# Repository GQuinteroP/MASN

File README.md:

# MASN: Mobile Acoustic Sensor Node

The **MASN** is an advanced, low-power sensor node designed for high-fidelity acoustic monitoring and long-range data transmission via NB-IoT. This repository contains the complete hardware design files, firmware, and configuration tools.

## Project Status: Minimal Working Version (MWV)
**Note:** The current firmware implementation is a **minimal working version**. While the hardware is fully featured, the firmware does not yet implement all architectural capabilities described in the documentation. Users are encouraged to consult the **Roadmap** below for contribution opportunities.

## Hardware Overview

The hardware architecture is optimized for power efficiency and modular operation, featuring a specialized dual-voltage design.

### Technical Specifications
* **Microcontroller:** STM32L452RET6P (Ultra-low-power ARM Cortex-M4).
* **Acoustic Sensing:** SPH0645LM4H MEMS microphone.
* **Positioning:** MAX-M10S-00B GNSS module.
* **Connectivity:** SIMCOM SIM7022 NB-IoT module.
* **Storage:** M95P32-IXMNT/E ultra-low-power EEPROM (32 Mbit).
* **Interface:** USB-C for parameter configuration, calibration, and data recovery.

### Architecture and PCB Design
The MASN is implemented on a double-sided printed circuit board (PCB). The architecture utilizes two isolated voltage domains:
1.  **1.8 V Domain (Front Face):** Powers the MCU, GNSS, microphone, and EEPROM.
2.  **2.1 V Domain (Back Face):** Powers the NB-IoT communication components.

---

## Firmware & Software

### Firmware Description (Current Implementation)
The firmware is built on **FreeRTOS**, following the architecture proposed in Quintero-Perez et al. (2026). It enables concurrent execution of four primary tasks:
* **Sampling:** Continuous audio acquisition using DMA and I2S protocol at $F_s = 32$ kHz.
* **Signal Processing:** Basic computation of $L_{Aeq}$ and OTOB indices ($L_{eq, f_c}$).
* **Georeferencing (GNSS):** Interfacing with the MAX-M10S module to retrieve latitude, longitude, satellite count (Sat#), and fix quality (Q). This metadata is integrated into the acoustic data blocks.
* **Transmission:** Support for network attachment and data delivery via **CoAP protocol** over NB-IoT.

### Configuration GUI
A Python-based GUI facilitates node management via USB-C:
* **Location:** `/Software/CONFIG_GUI`
* **Features:** Time synchronization, module management (GNSS/NB-IoT), and sensor calibration.

---

## Roadmap & Known Issues

### To-Do (Pending Features)
- [ ] **125 ms Sampling:** Implement granular chunking for high-resolution analysis.
- [ ] **IMEI Management:** Read IMEI once and store in non-volatile memory to reduce startup overhead.
- [ ] **Auto-Time Sync:** Automatic RTC configuration based on GNSS NMEA sentences.
- [ ] **EEPROM Integration:** Full implementation of data caching during network outages.

### Known Bugs & Technical Debt
- **Prescaler Drift:** Issues observed with prescaler stability over very long-term operation.
- **Communication Inefficiency:** Optimization required for both NB-IoT module and USB-C serial communication stacks.
- **Interrupt Overhead:** High processing load within `HAL_UART_RxCpltCallback`; logic needs to be migrated to task-level processing.

---

## Citation

If you use this hardware or software in your research, please cite the following paper:

> Quintero, G., Balastegui, A., & Romeu, J. (2026). **Autonomous mobile low-cost sensor node for high-resolution noise sampling in urban environments**. *Measurement*. (Accepted, pending publication).

---

## Licensing

### Hardware
Licensed under **CERN Open Hardware Licence Version 2 - Strongly Reciprocal (CERN-OHL-S)**.
* Full text: `docs/CERN-OHL-S.txt`

### Firmware & Software
Licensed under **GNU General Public License v3.0 (GPL-3.0)**.
* Full text: `docs/GNU GPL v3.txt`

---

## Repository Structure
* `/PCB`: Schematics, PCB design files, and BOM.
* `/Firmware`: Source code and build files for STM32.
* `/Software/CONFIG_GUI`: Python source code and UI files.
* `/docs`: Technical documentation, implementation images, and license files.

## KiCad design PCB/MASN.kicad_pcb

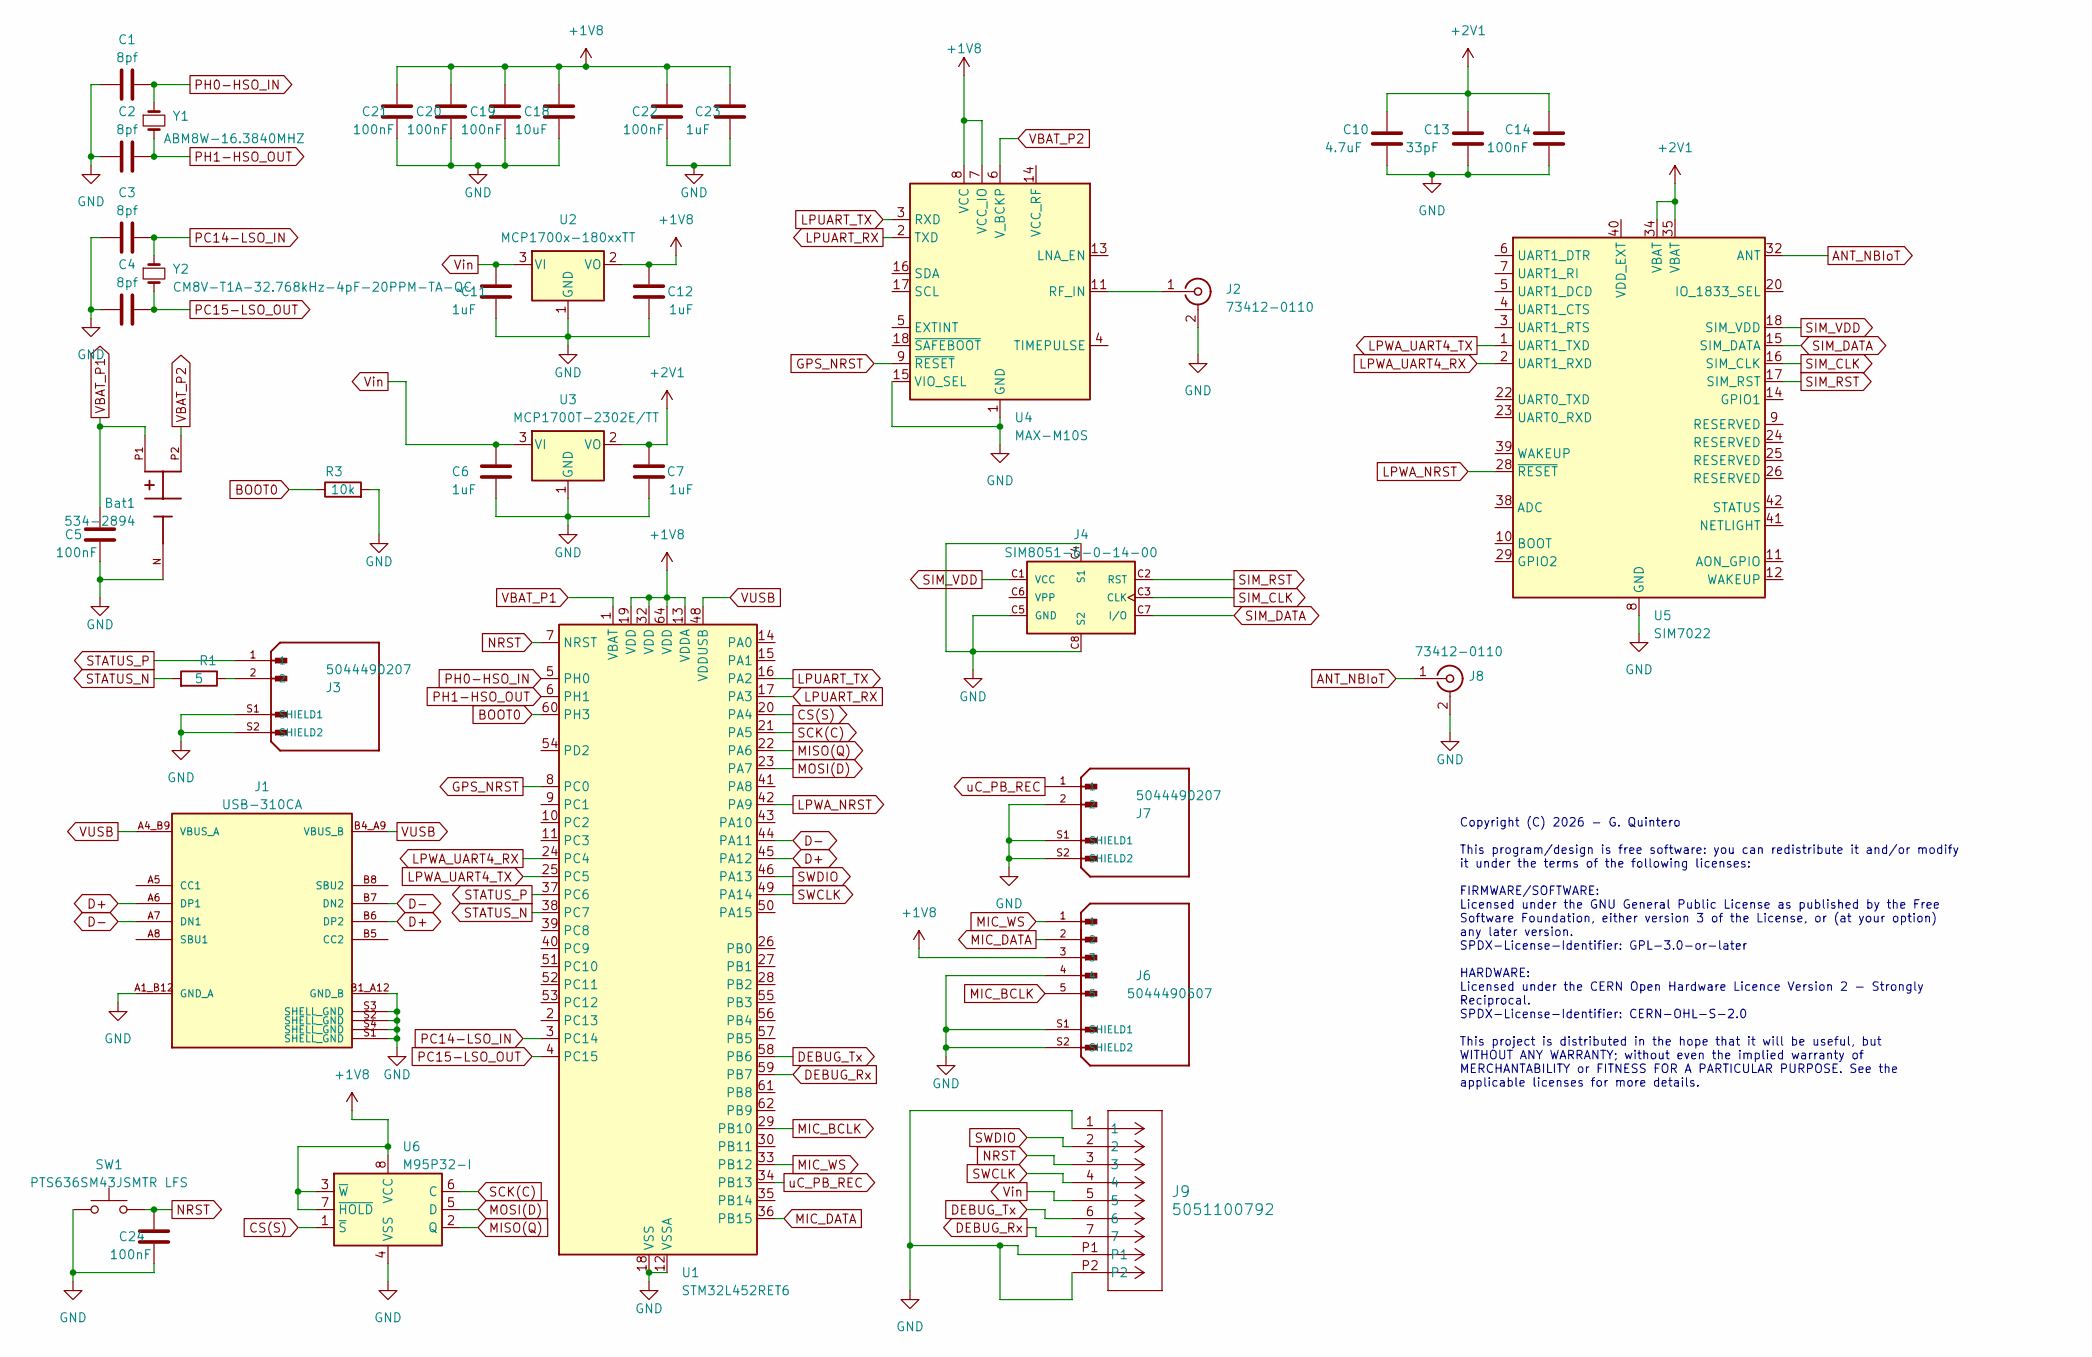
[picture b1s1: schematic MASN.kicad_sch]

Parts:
Bat1: 534-2894; BAT_2894; PARTREV B
C1, C2, C3, C4: 8pf; C_0603_1608Metric_Pad1.08x0.95mm_HandSolder
C5, C14, C19, C20, C21, C22, C24: 100nF; C_0603_1608Metric_Pad1.08x0.95mm_HandSolder
C6, C7, C11, C12, C23: 1uF; C_0603_1608Metric_Pad1.08x0.95mm_HandSolder
C10: 4.7uF; C_0603_1608Metric_Pad1.08x0.95mm_HandSolder
C13: 33pF; C_0603_1608Metric_Pad1.08x0.95mm_HandSolder
C18: 10uF; C_0603_1608Metric_Pad1.08x0.95mm_HandSolder
J1: USB-310CA; USB-C-SMD_20P-P0.50-L6.5-W11.2; PARTREV A
J2, J8: 73412-0110; U.FL_Molex_MCRF_73412-0110_Vertical
J3, J7: 5044490207; MOLEX_5044490207; PARTREV A
J4: SIM8051-6-0-14-00; GCT_SIM8051-6-0-14-00-X-REVD
J6: 5044490507; MOLEX_5044490507; PARTREV A
J9: 5051100792; CON_5051100792_MOL
R1: 5; R_0603_1608Metric_Pad0.98x0.95mm_HandSolder
R3: 10k; R_0603_1608Metric_Pad0.98x0.95mm_HandSolder
SW1: PTS636SM43JSMTR LFS; SW_SPST_CK_RS282G05A3
U1: STM32L452RET6; LQFP-64_10x10mm_P0.5mm
U2: MCP1700x-180xxTT; SOT-23
U3: MCP1700T-2302E/TT; SOT-23
U4: MAX-M10S; ublox_MAX
U5: SIM7022; SIMCom_SIM800C
U6: M95P32-I; SOIC-8_3.9x4.9mm_P1.27mm
Y1: ABM8W-16.3840MHZ; Crystal_SMD_Abracon_ABM8G-4Pin_Custom
Y2: CM8V-T1A-32.768kHz-4pF-20PPM-TA-QC; Crystal_SMD_MicroCrystal_CC8V-T1A-2Pin_2.0x1.2mm_HandSolder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

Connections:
+1V8: C12.2, C18.2, C19.2, C20.2, C21.2, C22.2, C23.2, J6.3, U1.13 (VDDA), U1.19 (VDD), U1.32 (VDD), U1.64 (VDD), U2.2 (VO), U4.7 (VCC_IO), U4.8 (VCC), U6.3 (~W), U6.7 (~HOLD), U6.8 (VCC)
+2V1: C7.2, C10.2, C13.2, C14.2, U3.2 (VO), U5.34 (VBAT), U5.35 (VBAT)
ANT_NBIoT: J8.1 (In), U5.32 (ANT)
BOOT0: R3.1, U1.60 (PH3)
CS(S): U1.20 (PA4), U6.1 (~S)
D+: J1.A6 (DP1), J1.B6 (DP2), U1.45 (PA12)
D-: J1.A7 (DN1), J1.B7 (DN2), U1.44 (PA11)
DEBUG_Rx: J9.7, U1.59 (PB7)
DEBUG_Tx: J9.6, U1.58 (PB6)
GND: Bat1.N, C1.2, C2.1, C3.2, C4.1, C5.1, C6.1, C7.1, C10.1, C11.1, C12.1, C13.1, C14.1, C18.1, C19.1, C20.1, C21.1, C22.1, C23.1, C24.1, J1.A1_B12 (GND_A), J1.B1_A12 (GND_B), J1.S1 (SHELL_GND), J1.S2 (SHELL_GND), J1.S3 (SHELL_GND), J1.S4 (SHELL_GND), J2.2 (Ext), J3.S1 (SHIELD1), J3.S2 (SHIELD2), J4.C4 (S1), J4.C5 (GND), J4.C8 (S2), J6.4, J6.S1 (SHIELD1), J6.S2 (SHIELD2), J7.2, J7.S1 (SHIELD1), J7.S2 (SHIELD2), J8.2 (Ext), J9.1, J9.P1, J9.P2, R3.2, SW1.1, U1.12 (VSSA), U1.18 (VSS), U1.31 (VSS), U1.47 (VSS), U1.63 (VSS), U2.1 (GND), U3.1 (GND), U4.1 (GND), U4.10 (GND), U4.12 (GND), U4.15 (VIO_SEL), U5.8 (GND), U5.13 (GND), U5.19 (GND), U5.21 (GND), U5.27 (GND), U5.30 (GND), U5.31 (GND), U5.33 (GND), U5.36 (GND), U5.37 (GND), U6.4 (VSS)
GPS_NRST: U1.8 (PC0), U4.9 (~RESET)
LPUART_RX: U1.17 (PA3), U4.2 (TXD)
LPUART_TX: U1.16 (PA2), U4.3 (RXD)
LPWA_NRST: U1.42 (PA9), U5.28 (~RESET)
LPWA_UART4_RX: U1.24 (PC4), U5.2 (UART1_RXD)
LPWA_UART4_TX: U1.25 (PC5), U5.1 (UART1_TXD)
MIC_BCLK: J6.5, U1.29 (PB10)
MIC_DATA: J6.2, U1.36 (PB15)
MIC_WS: J6.1, U1.33 (PB12)
MISO(Q): U1.22 (PA6), U6.2 (Q)
MOSI(D): U1.23 (PA7), U6.5 (D)
NRST: C24.2, J9.3, SW1.2, U1.7 (NRST)
unnamed: J2.1 (In), U4.11 (RF_IN)
unnamed: J3.2, R1.1
PC14-LSO_IN: C3.1, U1.3 (PC14), Y2.1
PC15-LSO_OUT: C4.2, U1.4 (PC15), Y2.2
PH0-HSO_IN: C1.1, U1.5 (PH0), Y1.1
PH1-HSO_OUT: C2.2, U1.6 (PH1), Y1.3
SCK(C): U1.21 (PA5), U6.6 (C)
SIM_CLK: J4.C3 (CLK), U5.16 (SIM_CLK)
SIM_DATA: J4.C7 (I/O), U5.15 (SIM_DATA)
SIM_RST: J4.C2 (RST), U5.17 (SIM_RST)
SIM_VDD: J4.C1 (VCC), U5.18 (SIM_VDD)
STATUS_N: R1.2, U1.38 (PC7)
STATUS_P: J3.1, U1.37 (PC6)
SWCLK: J9.4, U1.49 (PA14)
SWDIO: J9.2, U1.46 (PA13)
VBAT_P1: Bat1.P1, C5.2, U1.1 (VBAT)
VBAT_P2: Bat1.P2, U4.6 (V_BCKP)
VUSB: J1.A4_B9 (VBUS_A), J1.B4_A9 (VBUS_B), U1.48 (VDDUSB)
Vin: C6.2, C11.2, J9.5, U2.3 (VI), U3.3 (VI)
uC_PB_REC: J7.1, U1.34 (PB13)

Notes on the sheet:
Copyright (C) 2026 - G. Quintero This program/design is free software: you can redistribute it and/or modify it under the terms of the following licenses: FIRMWARE/SOFTWARE: Licensed under the GNU General Public License as published by the Free Software Foundation, either version 3 of the License, 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

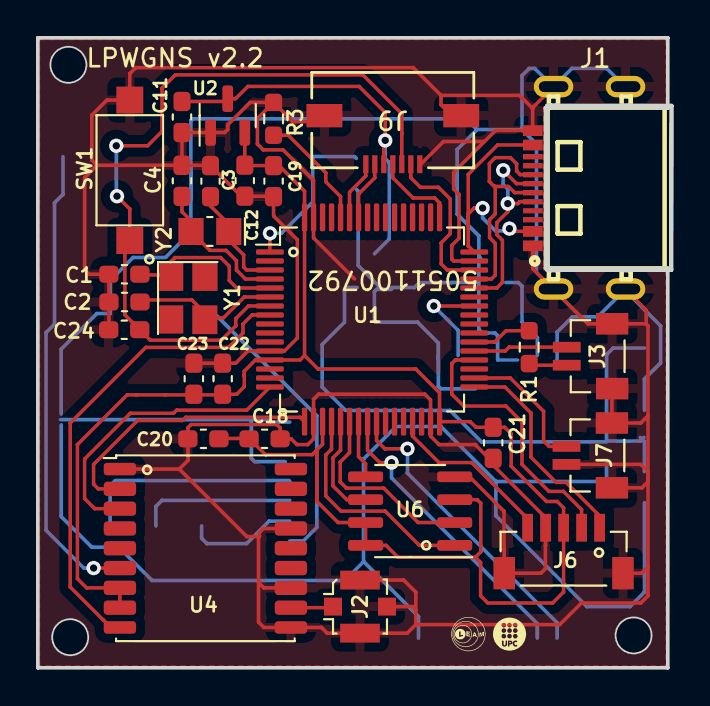
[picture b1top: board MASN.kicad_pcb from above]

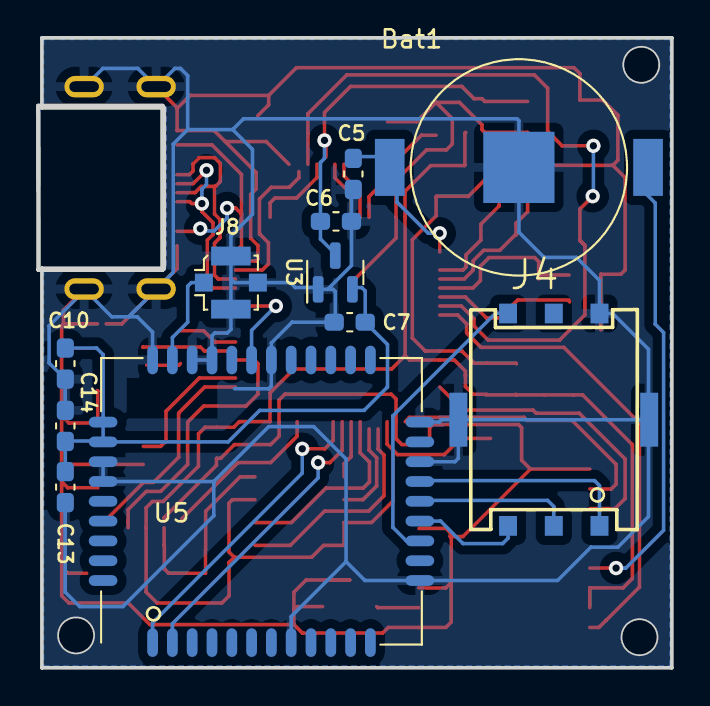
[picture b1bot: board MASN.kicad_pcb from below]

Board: 2 copper layers, 35.2 x 34.9 mm, 39 parts (11 on the bottom side), 42 nets.

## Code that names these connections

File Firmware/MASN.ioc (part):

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Mcu.Name=STM32L452R(C-E)Tx
Mcu.Package=LQFP64
Mcu.UserName=STM32L452RETx
PA11.Mode=Device
PA11.Signal=USB_DM
PA12.Mode=Device
PA12.Signal=USB_DP
PA13\ (JTMS/SWDIO).GPIOParameters=GPIO_Label
PA13\ (JTMS/SWDIO).GPIO_Label=TMS
PA13\ (JTMS/SWDIO).Mode=Serial_Wire
PA13\ (JTMS/SWDIO).Signal=SYS_JTMS-SWDIO
PA14\ (JTCK/SWCLK).GPIOParameters=GPIO_Label
PA14\ (JTCK/SWCLK).GPIO_Label=TCK
PA14\ (JTCK/SWCLK).Mode=Serial_Wire
PA14\ (JTCK/SWCLK).Signal=SYS_JTCK-SWCLK
PA2.GPIOParameters=GPIO_Label
PA2.GPIO_Label=LPUART_GPS_Tx
PA2.Mode=Asynchronous
PA2.Signal=LPUART1_TX
PA3.GPIOParameters=GPIO_PuPd,GPIO_Label
PA3.GPIO_Label=LPUART_GPS_Rx
PA3.GPIO_PuPd=GPIO_PULLUP
PA3.Mode=Asynchronous
PA3.Signal=LPUART1_RX
PA4.GPIOParameters=GPIO_Speed,PinState,GPIO_Label
PA4.GPIO_Label=SPI1_CS
PA4.GPIO_Speed=GPIO_SPEED_FREQ_VERY_HIGH
PA4.PinState=GPIO_PIN_RESET
PA4.Signal=GPIO_Output
PA5.GPIOParameters=GPIO_PuPd
PA5.GPIO_PuPd=GPIO_NOPULL
PA5.Mode=Full_Duplex_Master
PA5.Signal=SPI1_SCK
PA6.GPIOParameters=GPIO_PuPd
PA6.GPIO_PuPd=GPIO_NOPULL
PA6.Mode=Full_Duplex_Master
PA6.Signal=SPI1_MISO
PA7.GPIOParameters=GPIO_PuPd
PA7.GPIO_PuPd=GPIO_NOPULL
PA7.Mode=Full_Duplex_Master
PA7.Signal=SPI1_MOSI
PA9.GPIOParameters=GPIO_Speed,PinState,GPIO_PuPd,GPIO_Label
PA9.GPIO_Label=LPWA_NRST
PA9.GPIO_PuPd=GPIO_PULLUP
PA9.GPIO_Speed=GPIO_SPEED_FREQ_HIGH
PA9.PinState=GPIO_PIN_RESET
PA9.Signal=GPIO_Output
PB10.Mode=SAI_A_Master
PB10.Signal=SAI1_SCK_A
PB12.Mode=SAI_A_Master
PB12.Signal=SAI1_FS_A
PB13.GPIOParameters=GPIO_PuPd,GPIO_Label,GPIO_ModeDefaultEXTI
PB13.GPIO_Label=PB_REC
PB13.GPIO_ModeDefaultEXTI=GPIO_MODE_IT_FALLING
PB13.GPIO_PuPd=GPIO_PULLUP
PB13.Signal=GPXTI13
PB15.GPIOParameters=GPIO_Speed
PB15.GPIO_Speed=GPIO_SPEED_FREQ_LOW
PB15.Mode=SAI_A_Master
PB15.Signal=SAI1_SD_A
PB6.GPIOParameters=GPIO_Label
PB6.GPIO_Label=UART_DEBUG_Tx
PB6.Mode=Asynchronous
PB6.Signal=USART1_TX
PB7.GPIOParameters=GPIO_Label
PB7.GPIO_Label=UART_DEBUG_Rx
PB7.Mode=Asynchronous
PB7.Signal=USART1_RX
PC0.GPIOParameters=PinState,GPIO_PuPd,GPIO_Label
PC0.GPIO_Label=GPS_NRST
PC0.GPIO_PuPd=GPIO_NOPULL
PC0.PinState=GPIO_PIN_RESET
PC0.Signal=GPIO_Output
PC14-OSC32_IN\ (PC14).Mode=LSE-External-Oscillator
PC14-OSC32_IN\ (PC14).Signal=RCC_OSC32_IN
PC15-OSC32_OUT\ (PC15).Mode=LSE-External-Oscillator
PC15-OSC32_OUT\ (PC15).Signal=RCC_OSC32_OUT
PC4.Mode=Asynchronous
PC4.Signal=USART3_TX
PC5.Mode=Asynchronous
PC5.Signal=USART3_RX
PC6.GPIOParameters=GPIO_Label
PC6.GPIO_Label=STATUS_P
PC6.Signal=GPIO_Output
PC7.GPIOParameters=GPIO_Label
PC7.GPIO_Label=STATUS_N
PC7.Signal=GPIO_Output
PH0-OSC_IN\ (PH0).Mode=HSE-External-Oscillator
PH0-OSC_IN\ (PH0).Signal=RCC_OSC_IN
PH1-OSC_OUT\ (PH1).Mode=HSE-External-Oscillator
PH1-OSC_OUT\ (PH1).Signal=RCC_OSC_OUT
RCC.HSE_Timout=5000
RCC.HSE_VALUE=16384000
RCC.SYSCLKFreq_VALUE=16384000
RCC.SYSCLKSource=RCC_SYSCLKSOURCE_HSE
board=NUCLEO-L452RE
boardIOC=true

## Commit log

2026-02-05 Hardware commit (PCB)
2026-02-05 Licenses update
2026-02-05 Readme update
2026-02-05 Added doc folder
2026-02-05 Licenses moved
2026-02-05 Readme updated
2026-05-15 Delta-coding, automatic IMEI and timestamp working (1 s samples)
2026-05-15 Timeout bug solved
2026-05-15 Some bugs solved. 125 ms minimal working
2026-05-22 Some bugs solved. Working offline for different Leq integration times
2026-05-30 Long term GNSS crash when offline solved. Changed to circular DMA for GNSS
2026-06-11 GNSS lost signal crash when PSM activated solved
2026-06-16 GUI updated

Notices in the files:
PCB/MASN.kicad_pcb:
SPDX-License-Identifier: GPL-3.0-or-later
SPDX-License-Identifier: CERN-OHL-S-2.0
